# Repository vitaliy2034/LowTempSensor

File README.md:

# LowTempSensor
Low teperature high accuracy sensor

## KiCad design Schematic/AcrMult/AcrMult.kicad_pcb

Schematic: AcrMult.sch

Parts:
C1, C6: 0.1u; C_0603_1608Metric_Pad1.05x0.95mm_HandSolder
C2, C3: 22p; C_0603_1608Metric_Pad1.05x0.95mm_HandSolder
C4: 1u; C_0805_2012Metric_Pad1.15x1.40mm_HandSolder
C5: 10u; C_1206_3216Metric_Pad1.42x1.75mm_HandSolder
C7: 22u; C_1206_3216Metric_Pad1.42x1.75mm_HandSolder
C8: C10u; C_1206_3216Metric_Pad1.42x1.75mm_HandSolder
C9: 0.1u; C_0805_2012Metric_Pad1.15x1.40mm_HandSolder
D1: MINUSLED; LED_D3.0mm
D2: D; D_SMB
J1: Thermopara; TerminalBlock_4Ucon_1x02_P3.50mm_Horizontal
J2: VSel; PinHeader_1x03_P2.54mm_Vertical
J3: DIO_CLK(RX)_TX; PinHeader_1x03_P2.54mm_Vertical
J4: USB_B_Micro; USB_Micro-B_GCT_USB3076-30-A
J5: PowerBJ_Sw; BarrelJack_Wuerth_6941xx301002
R1: 7,5k; R_0805_2012Metric_Pad1.15x1.40mm_HandSolder
R2: 22; R_0805_2012Metric_Pad1.15x1.40mm_HandSolder
R3: 0; R_0805_2012Metric_Pad1.15x1.40mm_HandSolder
R4, R7: 51k; R_0805_2012Metric_Pad1.15x1.40mm_HandSolder
R5: 10k; R_0805_2012Metric_Pad1.15x1.40mm_HandSolder
R6: 15k; R_0805_2012Metric_Pad1.15x1.40mm_HandSolder
R8: 330k; R_0805_2012Metric_Pad1.15x1.40mm_HandSolder
R9: 1k2; R_0805_2012Metric_Pad1.15x1.40mm_HandSolder
R10, R11, R12, R13, R14, R15, R16, R17, R18: 470; R_0805_2012Metric_Pad1.15x1.40mm_HandSolder
R19, R20, R21, R23: 0; R_1206_3216Metric_Pad1.42x1.75mm_HandSolder
R22, R24: 0; R_1806_4516Metric_Pad1.57x1.80mm_HandSolder
TH1: 10k; RV_Disc_D12mm_W3.9mm_P7.5mm
U1: LT1498-MultComp; DIP-8_W7.62mm_LongPads
U2: CH340G; SOIC-16_3.9x9.9mm_P1.27mm
U3: STM32F030K6Tx; LQFP-32_7x7mm_P0.8mm
U4: CC56-12SRWA; CA56-12SRWA
U5: LT1762-3.3; MSOP-8_3x3mm_P0.65mm
U6: AP1117-33; SOT-223-3_TabPin2
Y1: 12Mhz; Crystal_SMD_HC49-SD

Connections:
+3.3VADC: C6.1, C8.1, R4.2, R5.1, R23.2, TH1.2, U1.8 (V+), U5.1, U5.2
+3V3: C7.1, J2.3, R22.1, U3.1, U3.17, U6.2
/A: R10.1, U4.11
/B: R18.1, U4.7
/C: R15.1, U4.4
/CC1: R21.1, U4.12
/CC2: U3.19, U4.9
/CC3: U3.21, U4.8
/CC4: U3.6, U4.6
/D: R13.1, U4.2
/DPX: R14.1, U4.3
/E: R12.1, U4.1
/F: R17.1, U4.10
/G: R11.1, U4.5
/MIN: D1.2, R16.1
/RX: U2.3, U3.29
/TX: U2.2, U3.30
ColdJunction: R6.1, R19.2, U1.7
GND: C1.2, C2.2, C3.2, C4.2, C5.2, C7.2, C8.2, C9.2, D1.1, J4.5, J4.6, J5.2, J5.3, R1.1, R2.2, R7.2, R9.2, U1.4 (V-), U2.1, U3.16, U3.31, U3.32, U5.4, U6.1
HotJunction: R8.1, R20.2, U1.1
unnamed: C1.1, J1.2, R2.1, R5.2
unnamed: C2.1, U2.8, Y1.1
unnamed: C3.1, U2.7, Y1.2
unnamed: C6.2, U5.3
unnamed: C9.1, U3.4
unnamed: D2.2, R24.2
unnamed: J1.1, U1.3 (+)
unnamed: J2.1, R23.1
unnamed: J2.2, U3.5
unnamed: J3.1, U3.25
unnamed: J3.2, U3.24
unnamed: J3.3, U3.23
unnamed: J4.1, R24.1
unnamed: J4.2, U2.6
unnamed: J4.3, U2.5
unnamed: R1.2, R3.2, TH1.1
unnamed: R3.1, R6.2, U1.6 (-)
unnamed: R4.1, R7.1, U1.5 (+)
unnamed: R8.2, R9.1, U1.2 (-)
unnamed: R10.2, U3.18
unnamed: R11.2, U3.7
unnamed: R12.2, U3.8
unnamed: R13.2, U3.9
unnamed: R14.2, U3.10
unnamed: R15.2, U3.11
unnamed: R16.2, U3.12
unnamed: R17.2, U3.20
unnamed: R18.2, U3.22
unnamed: R19.1, U3.14
unnamed: R20.1, U3.15
unnamed: R21.2, U3.13
unnamed: R22.2, U2.4, U2.16
VPP: C4.1, C5.1, D2.1, J5.1, U5.5, U5.8, U6.3

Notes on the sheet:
Power schematics
Hot junction
Cold junction

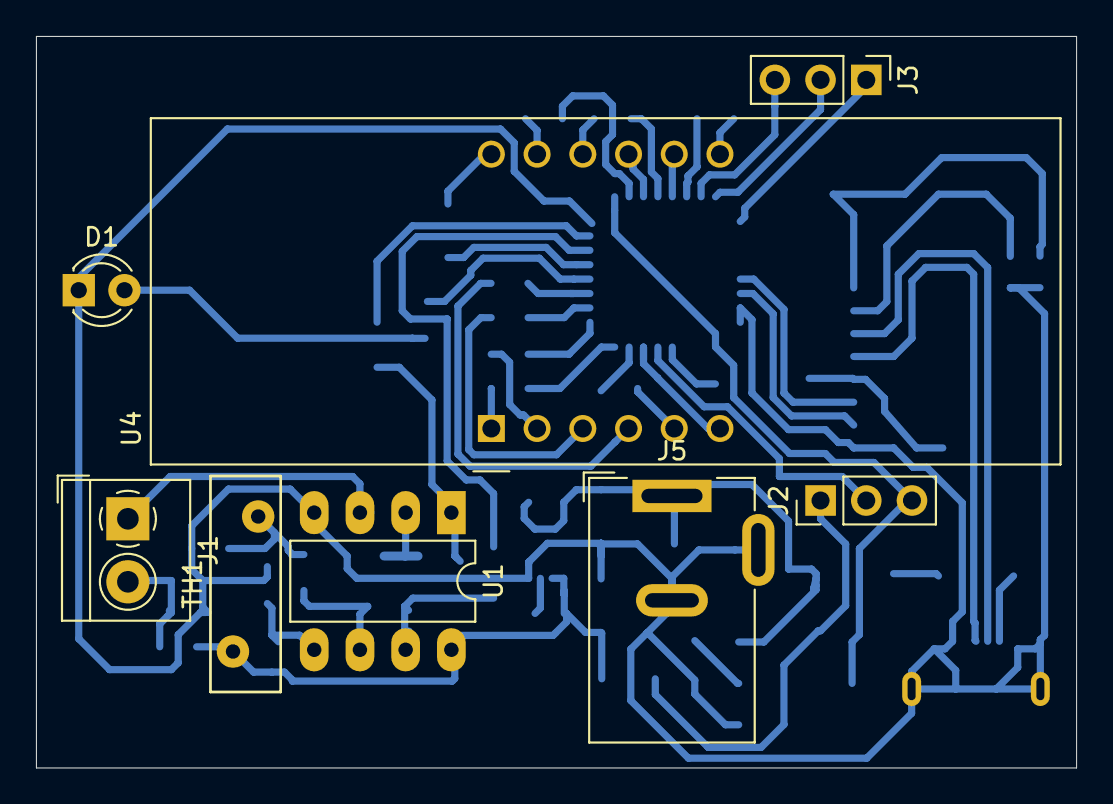
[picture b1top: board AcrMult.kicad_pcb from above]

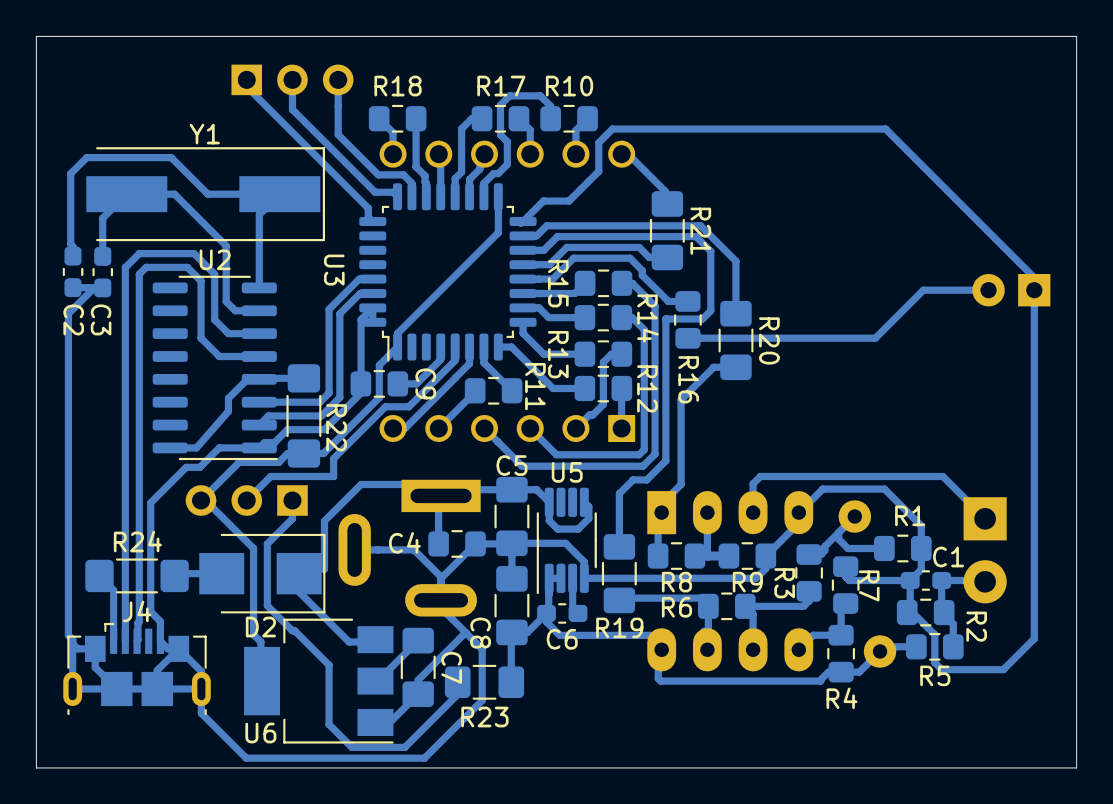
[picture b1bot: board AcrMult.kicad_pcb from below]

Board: 2 copper layers, 57.8 x 40.6 mm, 48 parts (40 on the bottom side), 53 nets.

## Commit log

2020-04-11 First Commit (added Information)
